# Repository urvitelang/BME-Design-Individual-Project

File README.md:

# BME-Design-Individual-Project
LED Twinkle Project

Project Specifics-to Design a self contained device with LED light that is button-activated to switch between the following operating modes:
Off
Brightest
Intermediate Brightness
Least Bright
Flashing @ 2 Hz

Constraints:
1.Run on single battery up to 9 V
2.Electronics connected to a single PCB (can be single- or double-sided)
3.Cannot weight more than 1 lb
4.Cannot have a single dimension > 6 in
5.Cannot cost more than $50 to duplicate unit
6.Battery must be easily replaceable

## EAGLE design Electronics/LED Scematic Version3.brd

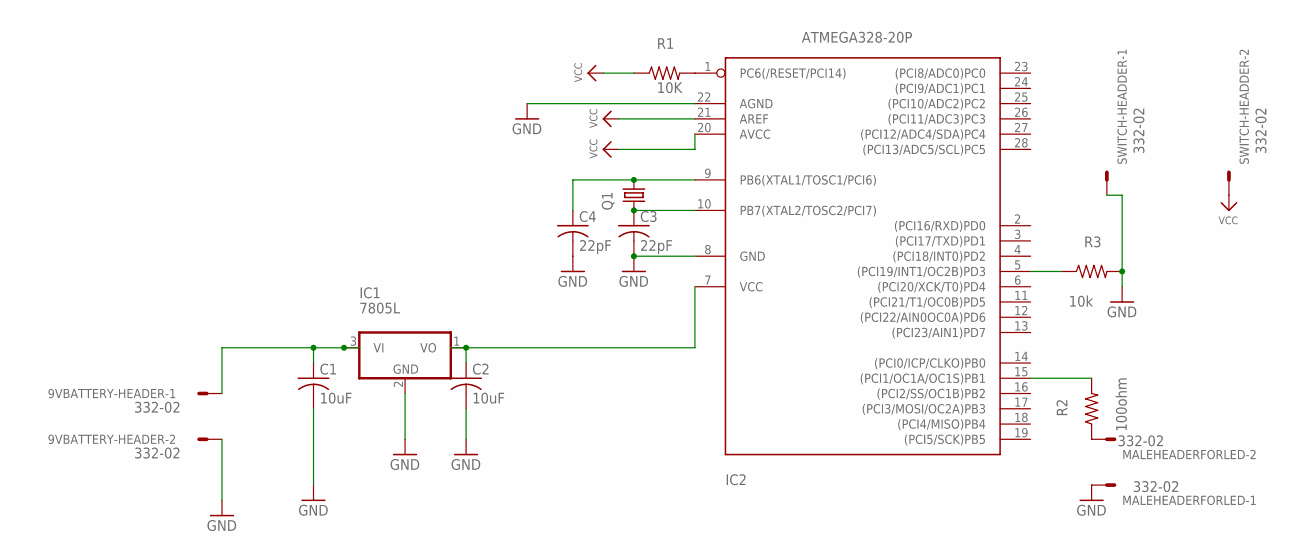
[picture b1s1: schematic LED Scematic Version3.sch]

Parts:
9VBATTERY-HEADER: 332-02
C1, C2: 10uF; C025-040X050
C3, C4: 22pF; C025-040X050
IC1: 7805L; TO92
IC2: ATMEGA328-20P; DIL28-3
MALEHEADERFORLED: 332-02
Q1: CRYSTALHC49S; HC49/S
R1: 10K; 0207/12
R2: 100ohm; 0207/12
R3: 10k; 0207/12
SWITCH-HEADDER: 332-02

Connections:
GND: 9VBATTERY-HEADER.2, C1.2, C2.2, C3.2, C4.2, IC1.2 (GND), IC2.8 (GND), IC2.22 (AGND), MALEHEADERFORLED.1, R3.2, SWITCH-HEADDER.1
unnamed: IC2.1 (PC6(/RESET/PCI14)), R1.2
unnamed: C4.1, IC2.9 (PB6(XTAL1/TOSC1/PCI6)), Q1.2
unnamed: C3.1, IC2.10 (PB7(XTAL2/TOSC2/PCI7)), Q1.1
unnamed: 9VBATTERY-HEADER.1, C1.1, IC1.3 (VI)
unnamed: C2.1, IC1.1 (VO), IC2.7 (VCC)
unnamed: IC2.5 ((PCI19/INT1/OC2B)PD3), R3.1
unnamed: IC2.15 ((PCI1/OC1A/OC1S)PB1), R2.2
unnamed: MALEHEADERFORLED.2, R2.1
VCC: IC2.20 (AVCC), IC2.21 (AREF), R1.1, SWITCH-HEADDER.2

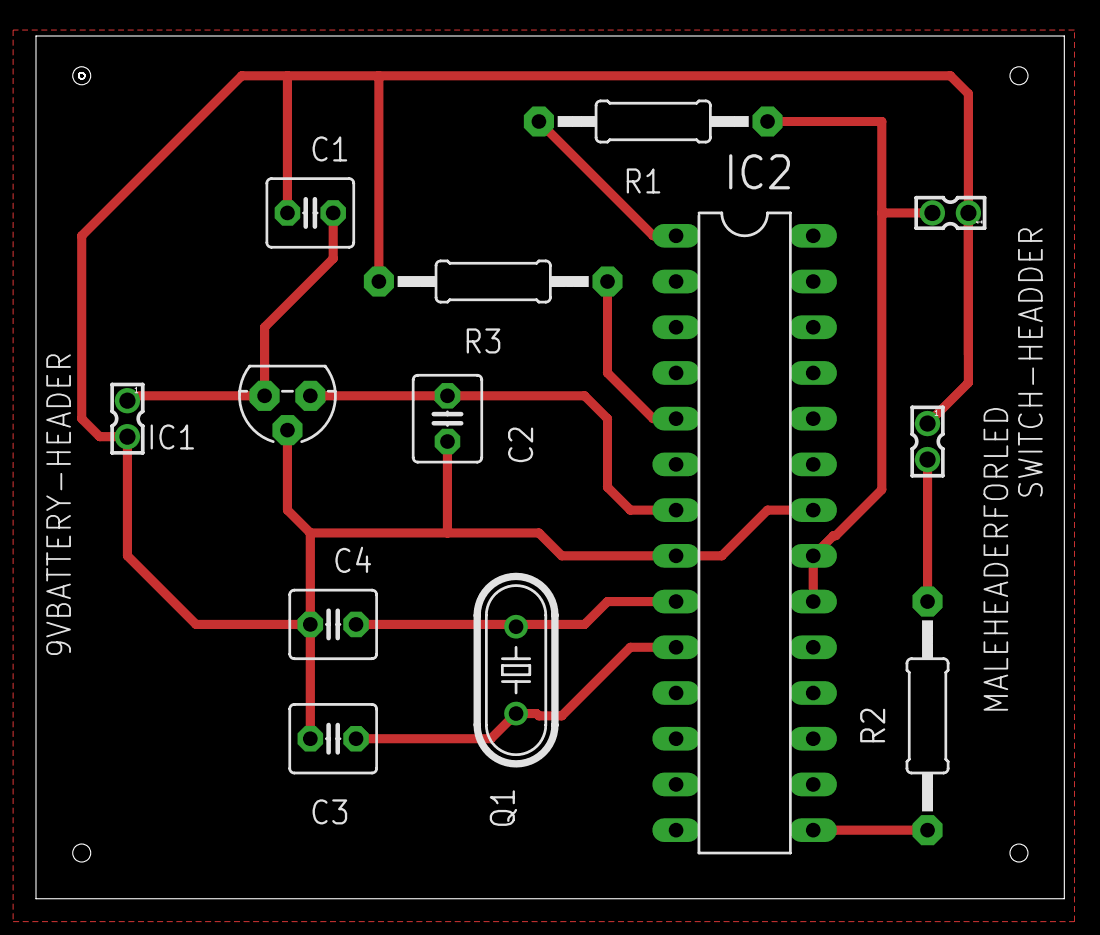
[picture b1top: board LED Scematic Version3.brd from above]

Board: 2 copper layers, 57.1 x 47.9 mm, 13 parts (0 on the bottom side), 10 nets.

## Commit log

2018-09-30 Project description added to the README.md file
2018-11-01 Create readme
    create Mechanical directory
2018-11-01 Create readme
    Create Electronics Directroy
2018-11-01 Create readme
    Create Software directory
2018-11-01 Create readme
    Create testing directory
2018-11-01 Create readme
    Create Docs directory
2018-11-01 Circuit Sechematic Version 01
2018-11-01 Add files via upload
    Software Flowchart Version 01
2018-11-08 Schematic LED version1 & PCB LED version1
2018-11-08 Part descriptions and packages used
2018-11-18 LED schematic and PCB version 2
2018-11-20 LED Project Schematic and PCB layout
2018-12-14 Snapfit Box Enclosure files
2018-12-14 Atmega328p datasheet
2018-12-14 Final PCB board layout and schematic
2018-12-14 Final LED code
